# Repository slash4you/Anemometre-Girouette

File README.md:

# Anémomètre+Girouette
Projet de construction DIY d'un anémomètre et d‘ une girouette connectés à Home Assistant.

## Caractéristiques principales 
|  | DIY | Conception |
|---|---|---|
|  | 100% imprimable (PETG ou ABS, TPU), compacte, alimentation par batterie 18650 au Lithium (3800mAh) , recharge par panneau solaire (2W), mesure de la vitesse du vent par capteur à effet hall, mesure de la direction du vent (en cours)  |   |
|  | assemblage par visserie standard, colle au silicone (étanchéité de la boite de commande), colle cyanoacrylate (selon l‘ ajustement des queues d‘ arronde) |   |
|  | composants low-cost, firmware opensource, connection WIFI au serveur domotique, esphome ready, optimisation de l‘ autonomie |   |
|  |   conception modifiable, évolutive, toutes les données partagées, personnalisable à volonté |   |

## GitHub

Ce dépôt regroupe l‘ ensemble des données nécessaires à la construction de cet anémomètre, organisées de la façon suivante:
+ [fusion360](https://github.com/slash4you/Anemometre-Girouette/blob/main/fusion360) → contient le modèle 3D au format f3d
+ [bambustudio](https://github.com/slash4you/Anemometre-Girouette/blob/main/bambustudio) → contient le modèle d ‘impression au format 3mf
+ [stl](https://github.com/slash4you/Anemometre-Girouette/blob/main/stl) → contient le fichier de maillage de chaque composant au format stl
+ [esphome](https://github.com/slash4you/Anemometre-Girouette/blob/main/esphome) → contient la description du firmware au format yaml
+ [images](https://github.com/slash4you/Anemometre-Girouette/blob/main/images) → contient un ensemble d ‘ images du modèle et photos du prototype
+ [kicad](https://github.com/slash4you/Anemometre-Girouette/blob/main/kicad)  → contient la définition du PCB au format kicad et gerber

## Makerworld

Le projet d‘ impression correspondant est disponible ici:  [Anémomètre+Girouette](https://makerworld.com/fr/models/2154241) .

## Avancement

Le premier objectif est la mise au point d‘ un prototype fonctionnel (version beta du projet), avant de capitaliser les informations et formaliser la documentation indispensable à une diffusion plus large (version release du projet). 

> Pour les impatients sachez que ce n ‘est pas l‘ envie qui fait défaut mais bien le temps... d‘ autant qu‘ il s‘ agit de ma première expérience en modélisation 3D, en conception de PCB, et que l‘ impression 3D est une expérience très récente. Toute aide est la bienvenue pour corriger, améliorer, tester.. bref partager.

### 1. Version beta (V0) : prototypage

- [x] 100%  : modélisation de la structure mécanique
- [x] 100%  : approvisionnement des composants tierces
- [x] 100%  : impression+assemblage de la structure mécanique
- [x] 100%  : assemblage des composants électroniques ( panneau solaire + calculateur + batterie + CI )
- [x] 100%  : développement du firmware du calculateur
- [x] 100% : intégration des capteurs de mesure de l‘ anémomètre
- [x] 100% : 🍾
- [x] 100% : intégration des capteurs de mesure de la girouette
- [x] 100% : 🍾
- [x] 100% : tests en environnement réel
- [x] 100% : 🎉

| | Réalisation |
|---|---|
|  |  |
|  |  |
|  | |

### 2. Retours d‘ expérience sur le prototype après 1 mois

Après un mois d‘ installation dans le jardin, l‘ heure des premiers retours sur l‘ anémomètre DIY est arrivée :

#### Étanchéité de la boite de commande
Même si j‘ avais anticipé cette problématique lors de la conception, l‘ étanchéité du design initial n‘ était pas au rendez-vous puisqu‘ une semaine de pluie continue a complètement noyé la boite de commande. L‘ électronique et l‘ eau n‘ ont pas fait bon ménage et un des roulements s‘ est même oxydé jusqu‘ au blocage de la rotation de l‘ axe de l‘ anémomètre.
Une mise à jour de la boite de commande et de son couvercle a résolu ce problème.

#### Sensibilité par vent faible
J‘ avais privilégié la robustesse comme profil d‘ impression, craignant une fragilité des éléments imprimés lors des fortes rafale de vent assez fréquentes dans notre région. Mais je n‘ avais pas anticipé que l‘ inertie induite par cet excédent de matière aurait une conséquence sur la sensibilité par vent faible.
Une mise à jour de la forme et de la masse des coupelles a légèrement amélioré ce point mais l‘ inertie devra encore être optimisée et les frottements lors de la rotation devront être diminués pour obtenir un résultat convenable.
En l‘ état les coupelles se mettent en mouvement à partir de 10km/h de vent environ. Ceci se visualise parfaitement dans l‘ historisation des mesures par des tranches temporelles à 0 km/h car la période actuelle est très peu ventée ( vitesse moyenne locale issue d‘ internet comprise entre 5km/h et 15km/h.

Parmi les axes d‘ amélioration :
* optimiser les dimensions et le taux de remplissage des éléments mobiles.
* améliorer le montage des roulements, voire le choix du nombre et du type de roulements pour limiter les frottements à la rotation.

#### Calibration RPM vs km/h
J‘ avais sous-estimé la problématique de calibration pour obtenir une estimation fiable de la vitesse du vent à partir de la vitesse de rotation de l‘ anémomètre. Cette problématique est d‘ autant plus exagérée dans mon cas que :
- le seul site d‘ installation dans mon jardin est trop protégé des vents.
- je suspecte que la compacité souhaitée pour cet anémomètre n‘ est pas idéal pour obtenir un flux d‘ air « laminaire », ou à minima le moins perturbé possible, indispensable pour des mesures fiables.

Pour l‘ instant je compense ceci par une table de calibration qui maximise exagérément les mesures, mais cette technique n‘ est pas viable pour un résultat convenable et surtout pas transposable pour quiconque utiliserait le firmware dans son contexte.

#### Électronique
L‘ électronique, et en particulier la gestion de l‘ énergie, sont en revanche une bonne surprise du projet. 
La stabilité de la communication avec le serveur domotique est au rendez-vous et la gestion de la charge de la batterie par le panneau solaire donne des résultats qui confirme la viabilité de la solution. 
Ce constat n‘ est sans doute pas étranger au fait que cette activité du projet est dans mes compétences.

#### Assemblage
La complexité de l‘ assemblage révèle mon inexpérience en matière de conception 3D. Il est évident que le montage pourrait être largement simplifié par une meilleure conception, le nombre de pièces et le volume de matière imprimable pourraient être rationalisés, et par conséquent le coût global de la solution optimisé.
Parmi les axes d‘ amélioration :
* simplifier le montage des roulements pour limiter le nombre de pièces, la nécessité d‘ un parallélisme entre-eux, ...
* rendre indépendant la fixation du corps de la girouette de celle de l‘ anémomètre.
* utiliser un matériau transparent pour certaines pièces.

### 3. Retours d‘ expérience sur le prototype après 3 mois

Après trois mois d‘ installation dans le jardin, de nouvelles conclusions s‘ imposent :

#### Sensibilité par vent faible

La sensibilité de l‘ anémomètre a grandement été améliorée par un ajustement non contraint de l‘ un des 2 paliers de roulement pour chaque axe, libérant les contraintes axiales et contribuant ainsi à :
* simplifier globalement l‘ assemblage : moins de précision nécessaire au réglage de la longueur entre roulements,  fermeture facilitée par une insertion de l‘ extrémité opposée plus libre.
* augmenter de façon significative la sensibilité par vent faible, jusqu‘ à atteindre la vitesse de marche, soit environ 5 km/h.
Je considère que la mise à jour de ces ajustements a complètement résolu ce problème.

#### Pas de codage de la mesure de direction

J‘ envisageais initialement une conception permettant la mesure de 8 directions par la girouette, mais le prix unitaire pour coder 8 pas m‘ a semblé disproportionné. J‘ ai donc réduit cette spécification à 4 directions seulement pour limiter le coût global de la solution.

#### Stabilité de fonctionnement

Le montage est finalement achevé et fonctionnel, et la stabilité de fonctionnement sur la période est plus que satisfaisante. Un seul bug a été observé en 3 mois d‘ utilisation, nécessitant un reboot manuel du microcontrôleur pour palier à une absence de réveil (i.e. sortie du deep-sleep). Je n‘ ai pas beaucoup d‘ informations pour en analyser la cause car le problème est apparu au milieu de la nuit et avec toutes les traces logicielles désactivées. Mais je ne pense pas que le hardware soit en cause.  
A ce stade je mets plutôt en doute un problème introduit par une mise à jour d‘ esphome qui a souvent évolué sur la période et de manière significative.

#### Précisions des mesures

En toute transparence la précision des mesures est en-deçà de ce que j‘ espérais initialement. Un travail supplémentaire devra être mené sur :
* le site d‘ installation (problème spécifique à mon contexte)
* la calibration des mesures de vitesse de vent
* le lissage de la direction du vent par intégration dans le temps

### 4. Retours d‘ expérience sur le prototype après 4 mois

#### Précisions des mesures

Pour améliorer la précision des mesures, une variante du support mural a été conçue pour diminuer les perturbations dans la circulation des masses d‘ air.

Ce nouveau support améliore un peu la précision des mesures, et en particulier la direction du vent, mais ne corrige pas le problème de fond de mon installation, la présence d‘ arbres à proximité dans toutes les directions .

### 5. Version release (V1) : partage et support

- [ ]    0%  : étalonnage des mesures et optimisation de leur durée d‘ intégration
- [ ]    0%  : optimisation de la charge en fonction de l‘ ensoleillement, de la saison, de l‘ heure, ...
- [ ]    0%  : publication d‘ un profil d‘ impression makerworld « plug-and-play »
- [x] 100%  : documentation/schéma électronique/inventaire des composants électroniques
- [ ]    0%  : documentation/inventaire des composants mécaniques
- [ ]    0%  : documentation/tutoriel de montage

#### Documentation

TODO

#### Inventaire des composants/matériaux

Pour quiconque se lancerait dans la construction, voici la liste des composants pour le PCB  :
| N° | Référence | Valeur/Modèle | Désignation |
|----------------|-----------|-------|---------|
| 1 | C1 | 100nF | [C_Disc_D3.0mm_W2.0mm_P2.50m](https://fr.aliexpress.com/item/32973259342.html) |
| 2 | C2 | 100µF | [CP_Radial_D6.3mm_P2.50mm](https://fr.aliexpress.com/item/1005002524973878.html) |
| 3 | R1 | 120KΩ | [R_Axial_DIN0414_L11.9mm_D4.5mm_P15.24mm_Horizontal](https://fr.aliexpress.com/item/1005007032692303.html) |
| 4 | R2 | 330Ω | [R_Axial_DIN0414_L11.9mm_D4.5mm_P15.24mm_Horizontal](https://fr.aliexpress.com/item/1005007032692303.html) |
| 5 | R3 | 120KΩ | [R_Axial_DIN0414_L11.9mm_D4.5mm_P15.24mm_Horizontal](https://fr.aliexpress.com/item/1005007032692303.html) |
| 6 | U1 | WeMos D1 mini pro | [WEMOS_D1_mini_light](https://fr.aliexpress.com/item/1005007475726143.html) |
| 7 | U2 | MCP1700-330 TO-92 | [TO-92_Inline](https://fr.aliexpress.com/item/1005007167297693.html) |
| 8 | Q1 | IRLZ44N TO-220 | [TO-220-3_Vertical](https://fr.aliexpress.com/item/1005007174659364.html) |
| 9 | TP1 | TP4056 USB-C | [TP4056_module](https://fr.aliexpress.com/item/1005006124994712.html) |
| 10 | J1 | XH2.54-2P | [JST_XH_B2B-XH-A_1x02_P2.50mm_Vertical](https://fr.aliexpress.com/item/1005004985397880.html) |
| 11 | J2 | PH2.0-2P | [JST_PH_B2B-PH-K_1x02_P2.00mm_Vertical](https://fr.aliexpress.com/item/1005007441813591.html) |
| 12 | J3 | PH2.0-5P | [JST_PH_B5B-PH-K_1x05_P2.00mm_Vertical](https://fr.aliexpress.com/item/1005007441813591.html) |
| 13 | J4 | PH2.0-5P | [JST_PH_B5B-PH-K_1x05_P2.00mm_Vertical](https://fr.aliexpress.com/item/1005007441813591.html) |
| 14 | J5 | XH2.54-2P | [PinHeader_1x02_P2.54mm_Vertical](https://fr.aliexpress.com/item/4000988113226.html) |

La liste des composants pour l‘ alimentation :
| N° | Qté | Valeur/Modèle | Désignation |
|---|---|---|---|
| 1 | 1| 18650 Lithium 3.7V 3800mAh XH2.54-2P | [Batterie Lithium](https://fr.aliexpress.com/item/1005007257546981.html)|
| 2 | 2| 5V 1W 107x61mm| [Panneaux solaires](https://fr.aliexpress.com/item/1005006711306491.html)|

La liste des composants pour les mesures :
| N° | Qté | Valeur/Modèle | Désignation |
|---|---|---|---|
|  1 | 1| KY-003 A3144|         [Capteur à effet hall](https://fr.aliexpress.com/item/1005007985856987.html)         |
|  2  | 2 |       Disque 5x3mm      |                                               [Aimants ferrite](https://fr.aliexpress.com/item/1005008858265927.html)                                               |
|   3  |  1 |         STM8-P4        |                                                 [Capteur magnétique  de direction](https://fr.aliexpress.com/item/1005004379591016.html)                                                 |

La liste des consommables pour l‘ impression 3D :
| N° | Qté | Valeur/Modèle | Désignation |
|---|---|---|---|
|  1 | NNNg| PETG HF|         [blanc](https://eu.store.bambulab.com/fr/products/petg-hf?id=49068714787164)         |
|  2  |   NNNg  |   PETG HF  |                                               [noir](https://eu.store.bambulab.com/fr/products/petg-hf?id=49068714754396)                                               |
|  3  |   NNNg  |   TPU  |                                               [noir](https://eu.store.bambulab.com/fr/products/tpu-95a-hf?id=47305218687324)                                               |

La liste des consommables pour l‘ anémomètre :
| N° | Qté | Valeur/Modèle | Désignation |
|---|---|---|---|
|  1 | 2| M4x200|         [Tiges filetées](https://fr.aliexpress.com/item/1005008105589322.html)         |
|  2  |   4  |   5x10x4mm  |                                               [Roulements](https://fr.aliexpress.com/item/1005007668446060.html)                                               |
|  3  |   N  |   M4  |                                               Ecrous                                               |
|   4  |   4   |    M3x30   |                                                  [Vis](https://fr.aliexpress.com/item/1005002011961287.html)                                                  |
|   5   |    4   |     M3    |                                                    Ecrous                                                   |
|   6  |   N   |    TODO   |                                                  TODO                                                  |

## Licence

L e projet est publié sous licence [Creative Commons Attribution-Noncommercial-Share Alike](https://github.com/slash4you/Anemometre-Girouette/blob/main/LICENSE.md).

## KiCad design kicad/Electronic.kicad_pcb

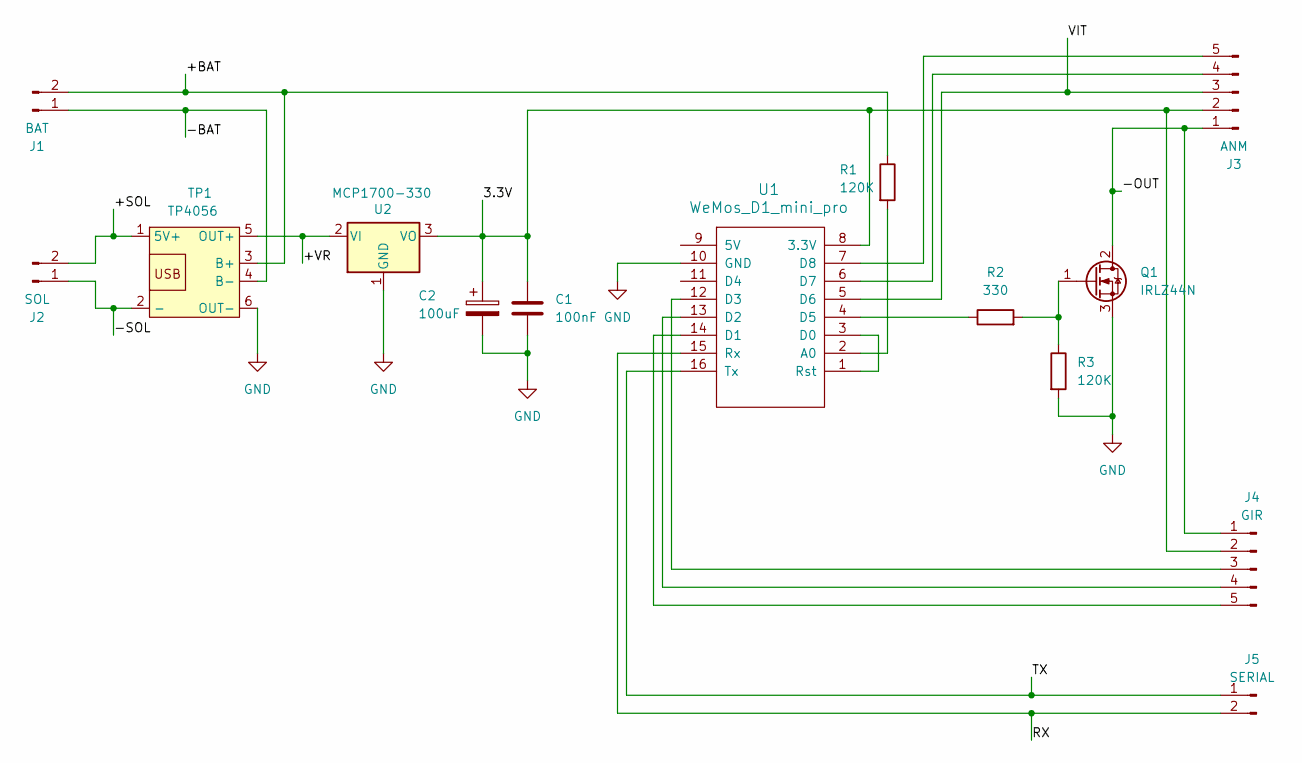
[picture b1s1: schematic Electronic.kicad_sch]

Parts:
C1: 100nF; C_Disc_D3.0mm_W2.0mm_P2.50mm
C2: 100uF; CP_Radial_D6.3mm_P2.50mm
J1: BAT; JST_XH_B2B-XH-A_1x02_P2.50mm_Vertical
J2: SOL; JST_PH_B2B-PH-K_1x02_P2.00mm_Vertical
J3: ANM; JST_PH_B5B-PH-K_1x05_P2.00mm_Vertical
J4: GIR; JST_PH_B5B-PH-K_1x05_P2.00mm_Vertical
J5: SERIAL; PinHeader_1x02_P2.54mm_Vertical
Q1: IRLZ44N; TO-220-3_Vertical
R1, R3: 120K; R_Axial_DIN0414_L11.9mm_D4.5mm_P15.24mm_Horizontal
R2: 330; R_Axial_DIN0414_L11.9mm_D4.5mm_P15.24mm_Horizontal
TP1: TP4056; TP4056_module
U1: WeMos_D1_mini_pro; WEMOS_D1_mini_light
U2: MCP1700-330; TO-92_Inline

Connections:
/3.3V: C1.1, C2.1, J3.2, J4.2, U1.8 (3.3V), U2.3 (VO)
/+BAT: J1.2, R1.1, TP1.3 (B+)
/+SOL: J2.2, TP1.1 (5V+)
/+VR: TP1.5 (OUT+), U2.2 (VI)
/-BAT: J1.1, TP1.4 (B-)
/-OUT: J3.1, J4.1, Q1.2 (D)
/-SOL: J2.1, TP1.2 (-)
/RX: J5.2, U1.15 (Rx)
/TX: J5.1, U1.16 (Tx)
/VIT: J3.3, U1.5 (D6)
GND: C1.2, C2.2, Q1.3 (S), R3.2, TP1.6 (OUT-), U1.10 (GND), U2.1 (GND)
unnamed: J3.4, U1.6 (D7)
unnamed: J3.5, U1.7 (D8)
unnamed: J4.3, U1.12 (D3)
unnamed: J4.4, U1.13 (D2)
unnamed: J4.5, U1.14 (D1)
unnamed: Q1.1 (G), R2.2, R3.1
unnamed: R1.2, U1.2 (A0)
unnamed: U1.1 (Rst), U1.3 (D0)
unnamed: R2.1, U1.4 (D5)

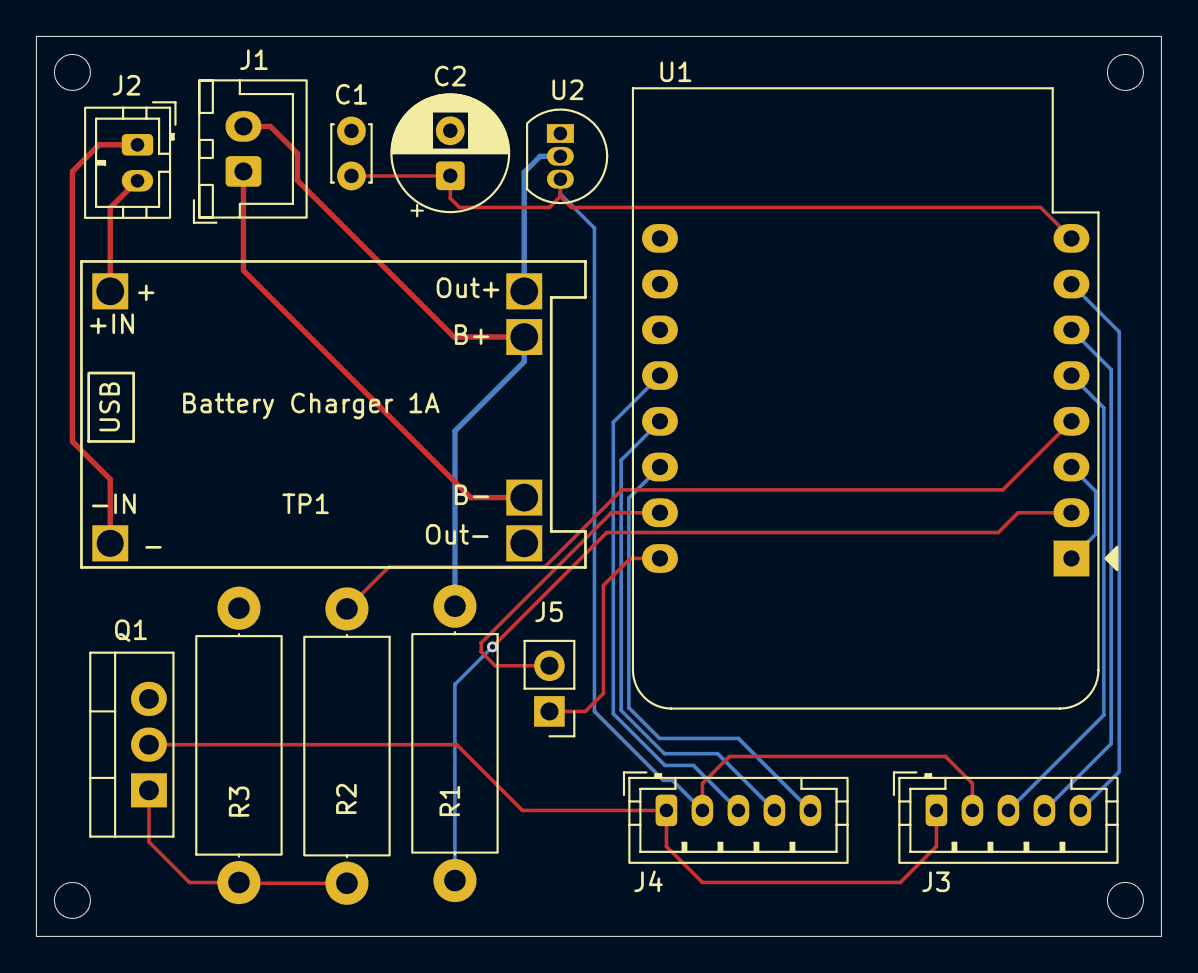
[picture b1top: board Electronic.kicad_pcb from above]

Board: 2 copper layers, 62.5 x 50.0 mm, 14 parts (0 on the bottom side), 20 nets.

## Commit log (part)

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2026-02-20 v345 : f3d/3mf/stl update
2026-02-20 v345 : png update
2026-02-21 v345 : images added
2026-02-21 v345 : yaml file added
2026-02-21 v345 : f3d file udpated
2026-02-22 v345 : license added and stl/images updated
2026-02-22 v345 : readme updated
2026-02-22 v345 : readme update
2026-03-14 v365 : us1881+magnets supports added
2026-03-14 v365 : us1881 support updated
2026-03-14 v365 : fusion360 model updated
2026-03-15 v372 - us1881 support updated
2026-03-15 v372 - readme updated
2026-03-15 v378 - anemometer body fixed
2026-03-15 v378 : readme updated
2026-03-19 v386 : bigger drill hole for cables
2026-04-03 v386 : electronix schematic added
2026-04-06 v386 : electronic schematic update
2026-04-10 v386 : pcb images updated
2026-04-10 v386 : pcb size increased
2026-04-11 v386 : gerber files exported from schematic
2026-04-11 v386 : electronic 3d model exported
2026-04-11 v388 : 3d models linked
2026-04-11 v388 : readme updated
2026-04-11 v389 : readme updated
2026-04-11 v389 : electronic schematic image added
2026-04-12 v389 : electronic pcb update
2026-04-12 v391 : eclectronic 3d model updated
2026-04-12 v399 : electronic 3d model support added
2026-04-12 v399 : readme updated
2026-04-12 v400 : readme updated
2026-04-14 v400 : pcb mounting supports added into control enclosure
2026-04-23 v419 : bigger drill holes for cables
2026-04-23 v419 : 3mf file updated
2026-04-24 v441 : bigger drill holes for cables
2026-04-26 v441 : more images uploaded
2026-04-26 v441 : wind speed sensor added into esphome firmware
2026-04-26 v441 : fix resistor values on PCB
2026-04-26 v441 : project progress updated into description
2026-05-01 v444 : image of anemometer installation on site added
2026-05-10 v480 : Fix control enclosure for better watertightness
2026-05-10 v480 : fix anemometer cups for better low-wind sensitivity
2026-05-14 v494 : Switch to conical cups to improve low-wind sensitivity
2026-05-14 v494 : esphome firmware updated
2026-05-31 v514 : wind direction sensor added
2026-05-31 v514 : esphome firmware updated
2026-05-31 v514 : images of home assistant dashboard added
2026-05-31 v514 : readme updated
2026-06-01 v514 : 3mf file updated
